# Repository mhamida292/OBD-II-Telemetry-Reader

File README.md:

# OBD-II Telemetry Reader

An OBD-II telemetry reader built with an ESP32 and designed in KiCAD.

## Overview

This project reads vehicle diagnostic data from the OBD-II port and displays it either on an LCD screen or streams it wirelessly via Bluetooth.

## Hardware

- **Microcontroller**: ESP32-S3 Rev 2
- **Design Software**: KiCAD 9
- **Input**: OBD-II connector (standard 16-pin)
- **Output Options**:
  - OLED display (I2C interface)
  - Bluetooth serial communication

## Features

- Real-time vehicle data monitoring
- Multiple data parameter support (RPM, speed, temperature, etc.)
- Wireless data transmission via Bluetooth
- Compact PCB design for automotive environment

## Future Enhancements

- WiFi data logging
- Mobile app integration
- Additional sensor support
- Data visualization dashboard

---

Built as a personal project.

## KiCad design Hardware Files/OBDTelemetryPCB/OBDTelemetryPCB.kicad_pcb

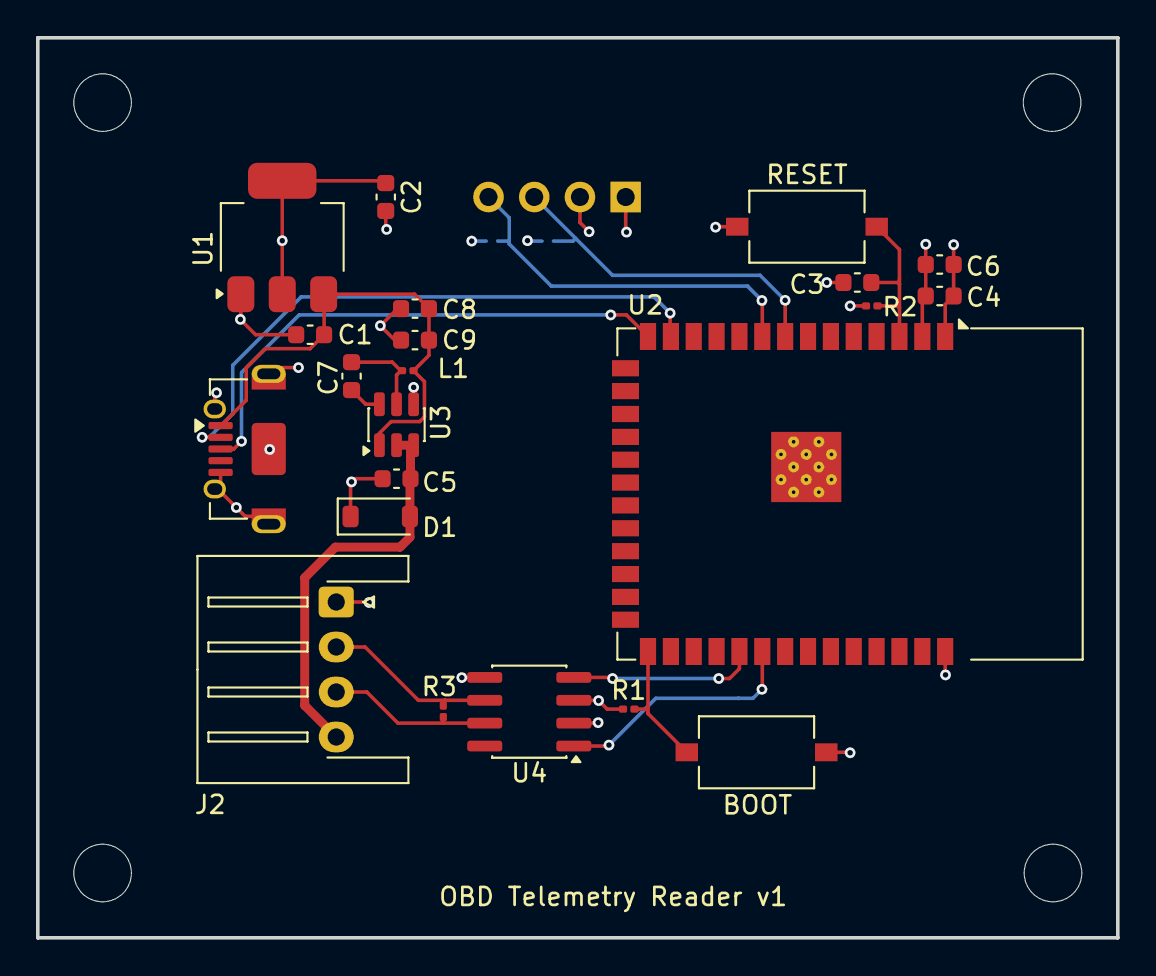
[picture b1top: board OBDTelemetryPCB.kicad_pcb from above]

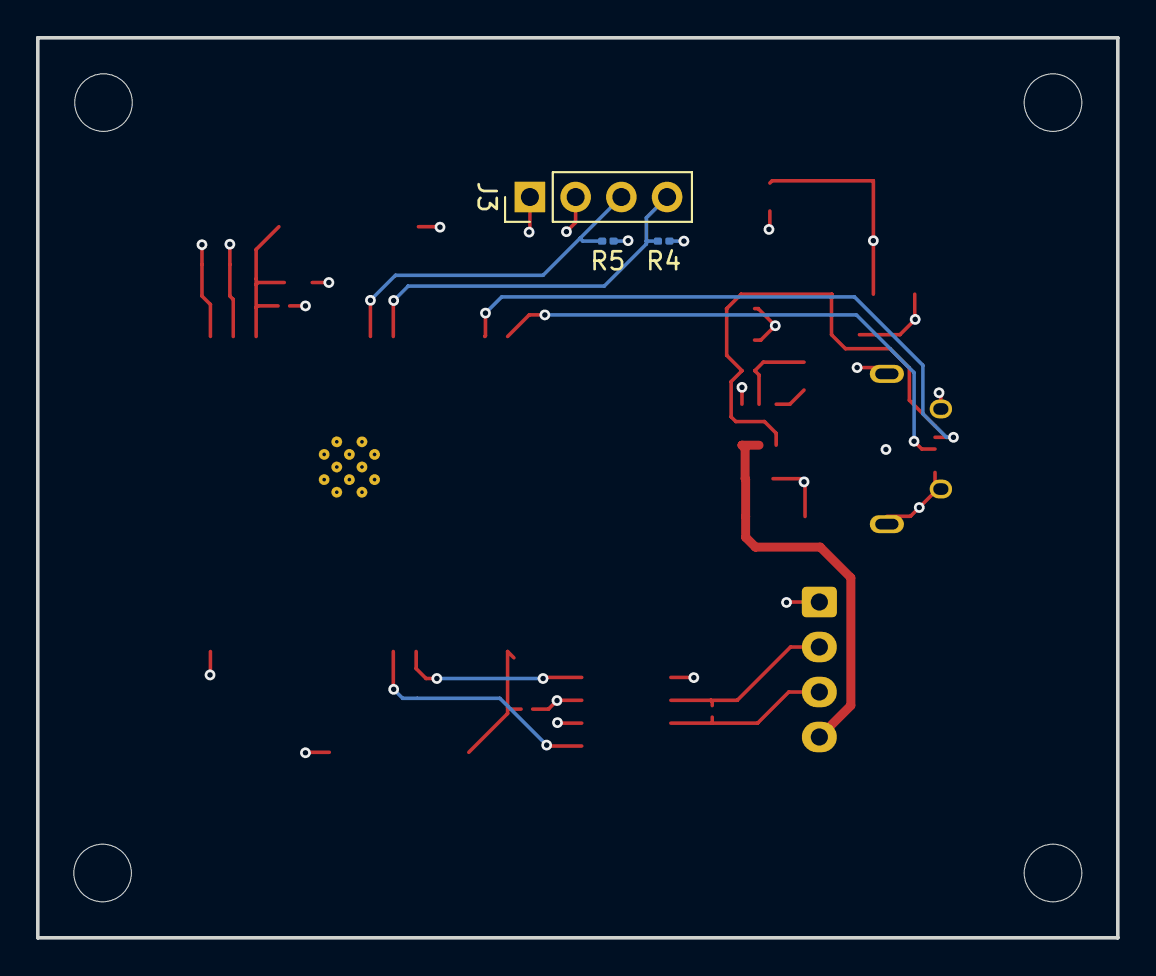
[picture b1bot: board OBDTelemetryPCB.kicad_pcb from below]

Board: 4 copper layers, 60.0 x 50.0 mm, 25 parts (3 on the bottom side), 16 nets.

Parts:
C1, C3: 1uF; C_0603_1608Metric
C2: 2.2uF; C_0603_1608Metric
C4: 0.1uF; C_0603_1608Metric
C5, C6: 10uF; C_0603_1608Metric
C7: 100nF; C_0603_1608Metric
C8, C9: 22uF; C_0603_1608Metric
D1: SM6T15A; D_SOD-123
J1: USB_B_Micro; USB_Micro-AB_Molex_47590-0001
J2: InputSocket; JST_XH_S4B-XH-A-1_1x04_P2.50mm_Horizontal
J3: Conn_01x04_Socket; PinHeader_1x04_P2.54mm_Vertical
L1: 4.7uH; R_0201_0603Metric
R1, R2: 10k; R_0201_0603Metric
R3: 120; R_0201_0603Metric
R4, R5: 4.7k; R_0201_0603Metric
SW1: BOOT; SW_Tactile_SPST_NO_Straight_CK_PTS636Sx25SMTRLFS
SW2: RESET; SW_Tactile_SPST_NO_Straight_CK_PTS636Sx25SMTRLFS
U1: TLV76133DCY; SOT-223-3_TabPin2
U2: ESP32-S3-WROOM-1
U3: AP63205WU; TSOT-23-6
U4: SN65HVD230; SOIC-8_3.9x4.9mm_P1.27mm

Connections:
+3.3V: C2.1, C4.1, C6.1, J3.2, R1.1, R2.1, R4.2, R5.2, U1.2 (VO), U2.2 (3V3), U4.3 (VCC)
+5V: C1.1, C8.2, C9.2, J1.1 (VBUS), L1.2, U1.3 (VI), U3.1 (FB)
+12V: C5.1, D1.2 (A2), J2.4, U3.2 (EN), U3.3 (IN)
/BOOT: R1.2, SW1.2, U2.27 (IO0)
/CANH: J2.3, R3.2, U4.7 (CANH)
/CANL: J2.2, R3.1, U4.6 (CANL)
/D+: J1.3 (D+), U2.14 (USB_D+)
/D-: J1.2 (D-), U2.13 (USB_D-)
/DTX: U2.32 (IO39), U4.1 (D)
/EN: C3.2, R2.2, SW2.2, U2.3 (EN)
/RTX: U2.31 (IO38), U4.4 (R)
/SCL: J3.3, R5.1, U2.8 (IO15)
/SDA: J3.4, R4.1, U2.9 (IO16)
GND: C1.2, C2.2, C3.1, C4.2, C5.2, C6.2, C8.1, C9.1, D1.1 (A1), J1.5 (GND), J1.6 (Shield), J2.1, J3.1, SW1.1, SW2.1, U1.1 (GND), U2.1 (GND), U2.40 (GND), U2.41 (GND), U3.4 (GND), U4.2 (GND), U4.5 (Vref)
unnamed: C7.2, U3.6 (BST)
unnamed: C7.1, L1.1, U3.5 (SW)

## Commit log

2025-12-26 V0.1 - Save Point
2025-12-27 Updated PCB
2026-04-01 Completed v1 of hardware
